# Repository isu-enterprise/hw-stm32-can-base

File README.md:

# Отладочная плата для хакинга CAN-шины

## Схема ....

### Useful docs

https://tuxotronic.org/post/mecrisp-forth/  (Loading programs via ```folie```)
https://github.com/juju2013/folie - folie

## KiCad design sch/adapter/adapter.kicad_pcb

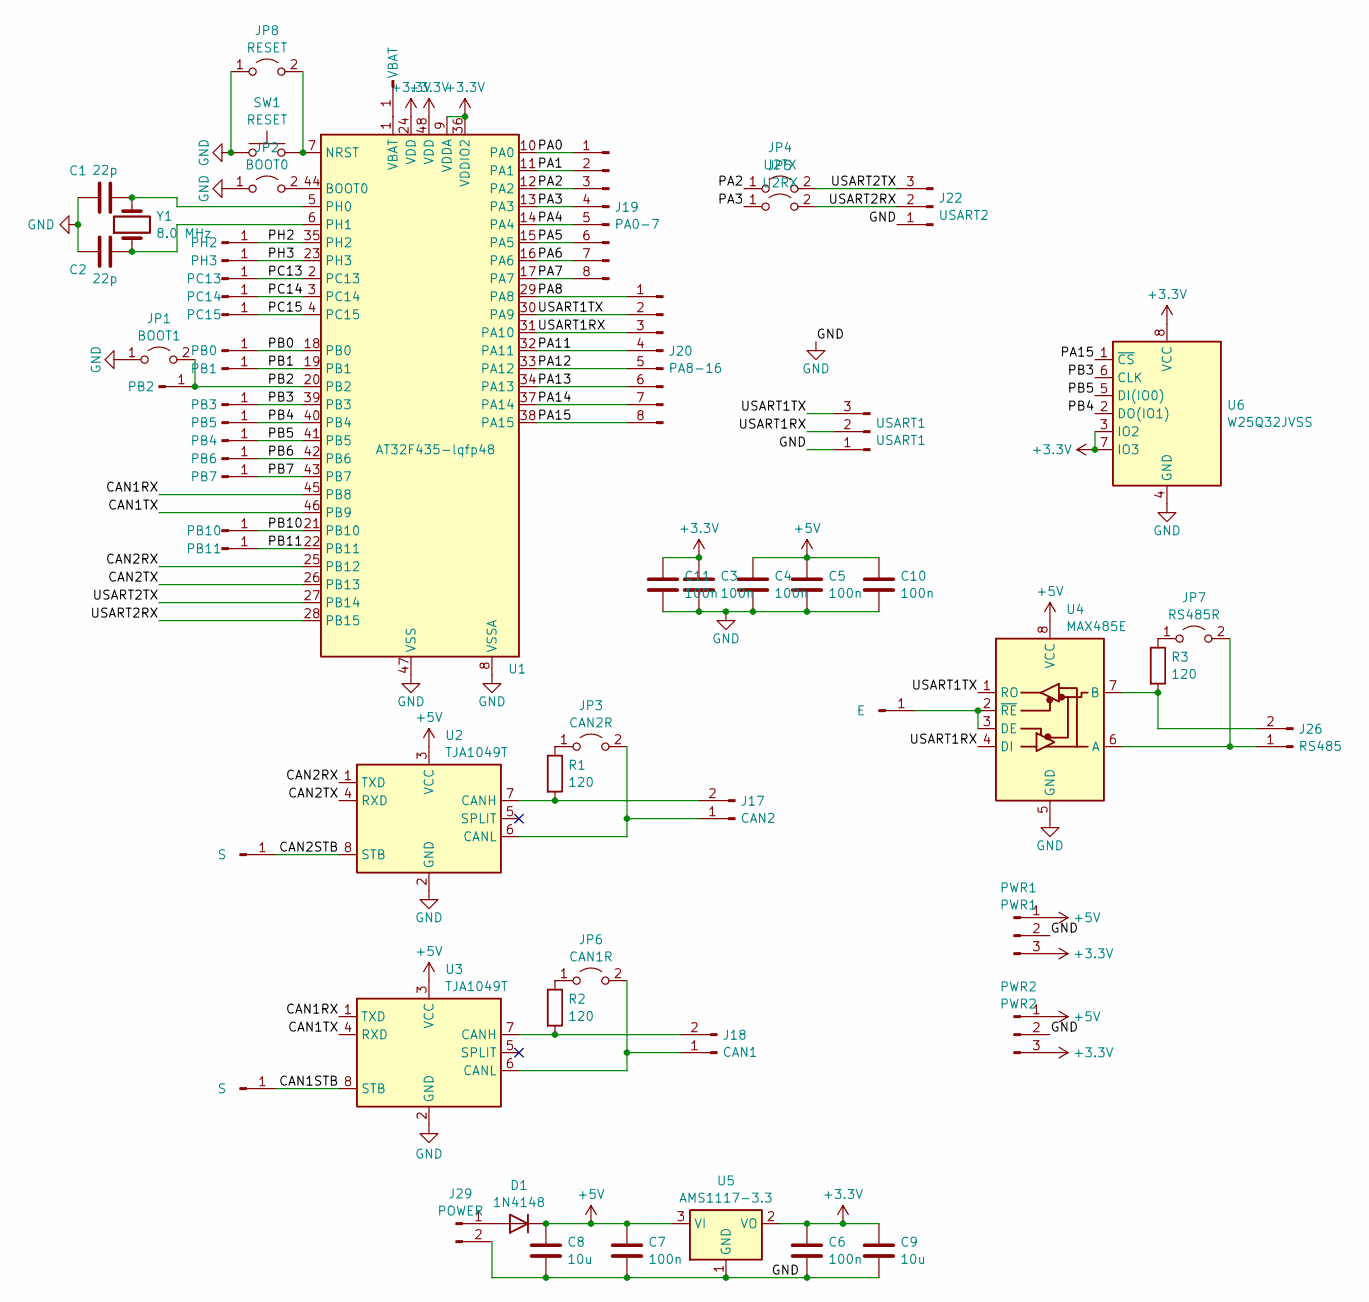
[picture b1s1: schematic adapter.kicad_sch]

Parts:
C1, C2: 22p; C_0805_2012Metric
C3, C4, C5, C6, C7, C10, C11: 100n; C_0805_2012Metric
C8, C9: 10u; C_0805_2012Metric
D1: 1N4148; D_DO-35_SOD27_P3.81mm_Vertical_KathodeUp
E: PinHeader_1x01_P2.54mm_Vertical
J17: CAN2; PinHeader_1x02_P2.54mm_Vertical
J18: CAN1; PinHeader_1x02_P2.54mm_Vertical
J19: PA0-7; PinHeader_1x08_P2.54mm_Vertical
J20: PA8-16; PinHeader_1x08_P2.54mm_Vertical
J22: USART2; PinHeader_1x03_P2.54mm_Vertical
J26: RS485; PinHeader_1x02_P2.54mm_Vertical
J29: POWER; PinHeader_1x02_P2.54mm_Vertical
JP1: BOOT1; PinHeader_1x02_P2.54mm_Vertical
JP2: BOOT0; PinHeader_1x02_P2.54mm_Vertical
JP3: CAN2R; PinHeader_1x02_P2.54mm_Vertical
JP4: U2TX; PinHeader_1x02_P2.54mm_Vertical
JP5: U2RX; PinHeader_1x02_P2.54mm_Vertical
JP6: CAN1R; PinHeader_1x02_P2.54mm_Vertical
JP7: RS485R; PinHeader_1x02_P2.54mm_Vertical
JP8: RESET; PinHeader_1x02_P2.54mm_Vertical
PB0, PB1, PB2, PB3, PB4, PB5, PB6, PB7, PB10, PB11: PinHeader_1x01_P2.54mm_Vertical
PC13, PC14, PC15: PinHeader_1x01_P2.54mm_Vertical
PH2, PH3: PinHeader_1x01_P2.54mm_Vertical
PWR1: PWR1; PinHeader_1x03_P2.54mm_Vertical
PWR2: PWR2; PinHeader_1x03_P2.54mm_Vertical
R1, R2, R3: 120; R_0805_2012Metric
S: PinHeader_1x01_P2.54mm_Vertical
SW1: RESET; SW_Push_SPST_NO_Alps_SKRK
U1: AT32F435-lqfp48; LQFP-48_7x7mm_P0.5mm
U2, U3: TJA1049T; SOIC-8_3.9x4.9mm_P1.27mm
U4: MAX485E; SOIC-8_3.9x4.9mm_P1.27mm
U5: AMS1117-3.3; SOT-223-3_TabPin2
U6: W25Q32JVSS; SOIC-8_5.23x5.23mm_P1.27mm
USART1: USART1; PinHeader_1x03_P2.54mm_Vertical
VBAT: PinHeader_1x01_P2.54mm_Vertical
Y1: 8.0 MHz; Crystal_HC49-4H_Vertical

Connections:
+3.3V: C3.1, C6.1, C9.1, C11.1, PWR1.3, PWR2.3, U1.9 (VDDA), U1.24 (VDD), U1.36 (VDDIO2), U1.48 (VDD), U5.2 (VO), U6.3 (IO2), U6.7 (IO3), U6.8 (VCC)
+5V: C4.1, C5.1, C7.1, C8.1, C10.1, D1.1 (K), PWR1.1, PWR2.1, U2.3 (VCC), U3.3 (VCC), U4.8 (VCC), U5.3 (VI)
/CAN1RX: U1.45 (PB8), U3.1 (TXD)
/CAN1TX: U1.46 (PB9), U3.4 (RXD)
/CAN2RX: U1.25 (PB12), U2.1 (TXD)
/CAN2TX: U1.26 (PB13), U2.4 (RXD)
/PA0: J19.1, U1.10 (PA0)
/PA1: J19.2, U1.11 (PA1)
/PA2: J19.3, JP4.1 (A), U1.12 (PA2)
/PA3: J19.4, JP5.1 (A), U1.13 (PA3)
/PA4: J19.5, U1.14 (PA4)
/PA5: J19.6, U1.15 (PA5)
/PA6: J19.7, U1.16 (PA6)
/PA7: J19.8, U1.17 (PA7)
/PA8: J20.1, U1.29 (PA8)
/PA11: J20.4, U1.32 (PA11)
/PA12: J20.5, U1.33 (PA12)
/PA13: J20.6, U1.34 (PA13)
/PA14: J20.7, U1.37 (PA14)
/PA15: J20.8, U1.38 (PA15), U6.1 (~CS)
/PB0: PB0.1, U1.18 (PB0)
/PB1: PB1.1, U1.19 (PB1)
/PB2: JP1.2 (B), PB2.1, U1.20 (PB2)
/PB3: PB3.1, U1.39 (PB3), U6.6 (CLK)
/PB4: PB5.1, U1.40 (PB4), U6.2 (DO(IO1))
/PB5: PB4.1, U1.41 (PB5), U6.5 (DI(IO0))
/PB6: PB6.1, U1.42 (PB6)
/PB7: PB7.1, U1.43 (PB7)
/PB10: PB10.1, U1.21 (PB10)
/PB11: PB11.1, U1.22 (PB11)
/PC13: PC13.1, U1.2 (PC13)
/PC14: PC14.1, U1.3 (PC14)
/PC15: PC15.1, U1.4 (PC15)
/PH2: PH2.1, U1.35 (PH2)
/PH3: PH3.1, U1.23 (PH3)
/USART1RX: J20.3, U1.31 (PA10), U4.4 (DI), USART1.2
/USART1TX: J20.2, U1.30 (PA9), U4.1 (RO), USART1.3
/USART2RX: J22.2, JP5.2 (B), U1.28 (PB15)
/USART2TX: J22.3, JP4.2 (B), U1.27 (PB14)
GND: C1.1, C2.1, C3.2, C4.2, C5.2, C6.2, C7.2, C8.2, C9.2, C10.2, C11.2, J22.1, J29.2, JP1.1 (A), JP2.1 (A), JP8.1 (A), PWR1.2, PWR2.2, SW1.1, U1.8 (VSSA), U1.47 (VSS), U2.2 (GND), U3.2 (GND), U4.5 (GND), U5.1 (GND), U6.4 (GND), USART1.1
unnamed: D1.2 (A), J29.1
unnamed: U1.1 (VBAT), VBAT.1
unnamed: J17.1, JP3.2 (B), U2.6 (CANL)
unnamed: J17.2, R1.2, U2.7 (CANH)
unnamed: J18.1, JP6.2 (B), U3.6 (CANL)
unnamed: J18.2, R2.2, U3.7 (CANH)
unnamed: E.1, U4.2 (~RE), U4.3 (DE)
unnamed: J26.1, JP7.2 (B), U4.6 (A)
unnamed: J26.2, R3.2, U4.7 (B)
unnamed: JP2.2 (B), U1.44 (BOOT0)
unnamed: JP3.1 (A), R1.1
unnamed: JP6.1 (A), R2.1
unnamed: JP7.1 (A), R3.1
unnamed: JP8.2 (B), SW1.2, U1.7 (NRST)
unnamed: C1.2, U1.5 (PH0), Y1.2
unnamed: C2.2, U1.6 (PH1), Y1.1

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
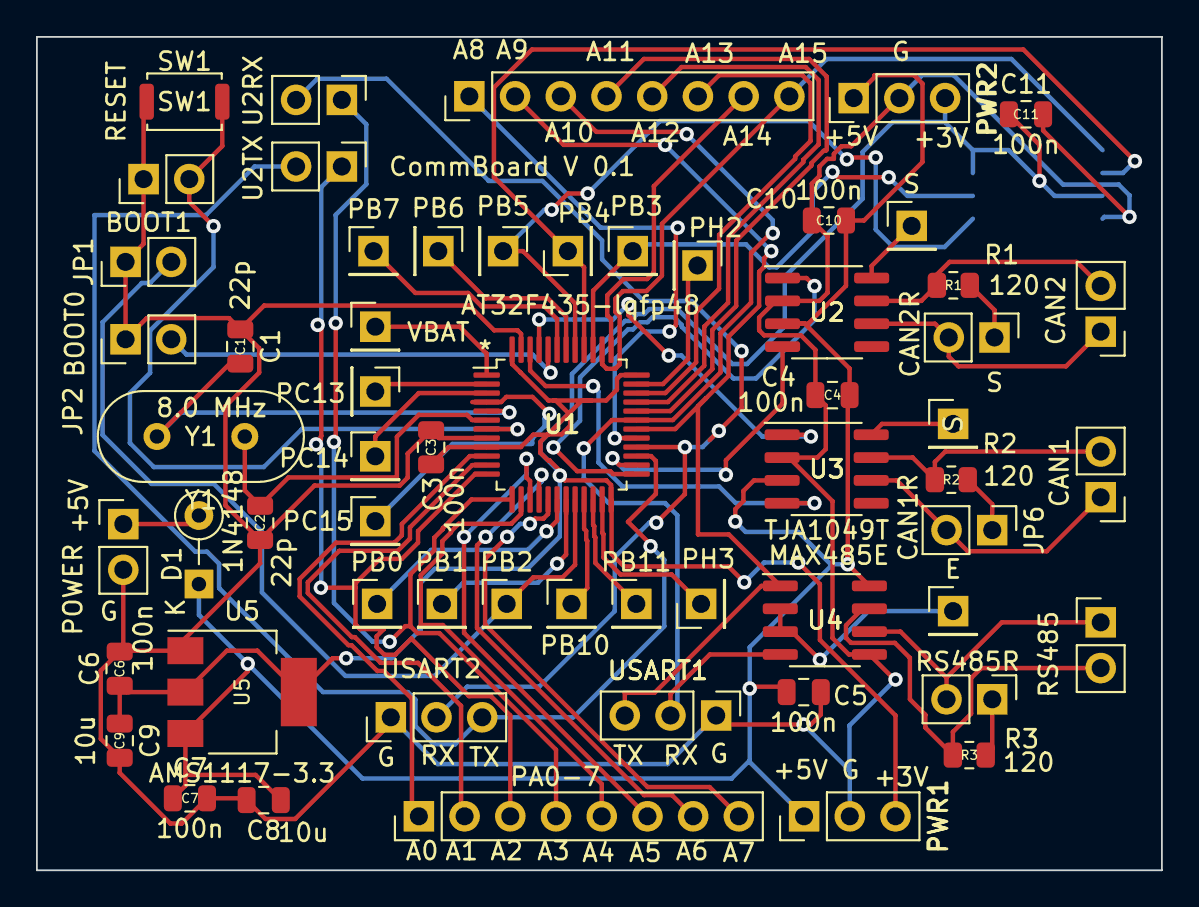
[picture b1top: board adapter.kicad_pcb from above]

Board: 2 copper layers, 62.5 x 46.3 mm, 60 parts (1 on the bottom side), 58 nets.

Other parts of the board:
S#2: PinHeader_1x01_P2.54mm_Vertical

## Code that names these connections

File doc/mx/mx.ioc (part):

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Mcu.Name=STM32F411C(C-E)Ux
Mcu.Package=UFQFPN48
Mcu.UserName=STM32F411CEUx
PA2.Mode=Asynchronous
PA2.Signal=USART2_TX
PA3.Mode=Asynchronous
PA3.Signal=USART2_RX
PA4.Signal=SPI1_NSS
PA5.Mode=Full_Duplex_Slave
PA5.Signal=SPI1_SCK
PA6.Mode=Full_Duplex_Slave
PA6.Signal=SPI1_MISO
PA7.Mode=Full_Duplex_Slave
PA7.Signal=SPI1_MOSI
PC13-ANTI_TAMP.Signal=GPIO_Output
PC14-OSC32_IN.Signal=GPIO_Output
PC15-OSC32_OUT.Signal=GPIO_Output
RCC.HSE_VALUE=25000000
RCC.SYSCLKFreq_VALUE=16000000
board=custom

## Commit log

2021-08-07 Added STM32F411 stuff to pivot to cardio.
2021-08-11 Test of led is successful.
2021-08-11 Added a figure for what....
2021-08-13 Implemented blinky
2021-08-13 Added a figure.
2021-08-13 First success of spi initialization
2021-08-14 Code generated by CubeMX
2021-08-14 Added normal/awesome book on STM32
2021-08-14 No track drivers, which were downloaded
2021-08-17 More info and SVGs of PCB.
2021-08-17 Added program for AD73360
2021-08-17 Added I2C for PCF8574t abd ILI9488
2021-08-17 Mapped Ports for TFT
2021-08-17 Added a register for RCC to support enabling I2C1
2021-08-18 Added SPI3 implementatio for 74LS595
2021-08-18 Refined setups.
2021-10-28 Correct Bug of WRONG AF code to 6
2021-10-28 Date stamp
2021-10-28 New Doc added.
2021-10-30 Added non-working MCP23s17 driver
2021-10-30 Corrected a bug in bit clearing
2021-10-30 Corrected number formats.
2021-10-31 MCP now work with big delays due to slow CS control.
2021-10-31 Now communication is working.
2021-10-31 Set a set of register names.
2021-10-31 Done with protocol implementation.
2021-10-31 Marked similar ili9488 functions with !
2021-10-31 Found an init sequence for ili9488!
2021-11-01 Initial sequence for ili9488
2021-11-01 It works, but color coding is mystical.
2021-11-07 Trying to get back to Shift register.
2021-11-08 Final stupidity finished.
2021-11-09 Working 595.
2021-11-11 Wrong clear direction
2021-11-11 Added tft implementation for 595 register. Does not work.
2021-11-11 Colors seem to work in inverse mode.
2021-11-11 Implemented alternation of registers when writing in MCP23S17.
2021-11-11 Made conserve protocol for pixel.
2021-11-12 Implemented filling rectangles.
2021-11-12 H- and V-lines now work
2021-11-13 Added compressed font.
2021-11-13 Allow font to go to flash.
2021-11-13 Font now in flash
2021-11-13 Removed wrong font
2021-11-13 Now we can print characters.
2021-11-14 Implemented typing.
2021-11-14 File Names refactoring
2021-11-17 Fixed comments for new Mecrisp Forth input buffer size
2021-11-17 Added possible location of folie sources
2021-11-17 Added CR, PLLCFG and CFG of RCC.
2021-11-17 Indexing of font.
2021-11-29 Tested spi.
2021-12-01 Swaped screen directions
2021-12-03 Started to implement h3 connection with stm32
2021-12-08 Added server directory
2021-12-08 Added template of api
2021-12-08 Added requirements -r
2021-12-08 Added api tests
2021-12-08 Provided run with Makefile
2021-12-10 Implemented tty interface as RESTF POST command
2021-12-10 Tests for FORTH endpoint
2021-12-14 Added forth code loading facility.
2021-12-14 Copies of classes
2021-12-14 Controlling server.
2021-12-14 Cleaned repetitions.
2021-12-14 Better error display
2021-12-14 Added finally buffer drawing.
2021-12-15 Added diploma ECG text.
2021-12-15 Now we can receive byte data!
2021-12-17 Addeded pictures of signals
2021-12-17 Added Pillow to requirements
2021-12-17 Added CLI fetures
2021-12-18 Now we can send and draw on the screen.
2021-12-18 Removed Todos.
2021-12-18 Now pictures are generated in correct bit order
2021-12-18 Added screen painting
2022-01-25 School network setup
2023-08-05 Cleaning the further unneeded data and sources
2023-08-05 Cleaning more unneeded data and sources
2023-08-05 Moved old code to a folder.
2023-08-05 Moved library as well.
2023-08-06 Added library files and gpio.
2023-08-06 Bug fixed and blinky test created.
2023-08-06 Added system setup stuff.
2023-08-06 Started SPI subsys.
2023-08-06 Transformed SPI driver from early implementations.
2023-08-07 Reorganize loading, libraries, bug fixed.
2023-08-07 Comments added.
2023-08-07 Bug in print word corrected.
2023-08-07 Implemented the command set for MCP-SPI-CAN device.
2023-08-07 Added docs for MCP2515 MCU-SPI-CAN interface.
2023-08-07 Bug fixed.
2023-08-07 Bug fixed. STM32F106 refuses to work. Shifting to F401.
2023-08-07 Added refman for dtm32f401cc.
2023-08-07 Adopted partially to F401 architecture.
2023-08-07 Added docs for F072 architecture.
2023-08-07 Further adaptation to F401
2023-08-07 Pin configuration
2023-08-14 MCP communications are OK now. Dump worked.
2023-08-14 Added docs for ARTERY chips at324xx LQFP48
2023-08-15 Added schematics.
2023-08-15 Ignoring gerbers, etc.
2023-08-15 Load SPI driver into flash, parametrized mcp access.
2023-08-15 Preparing SilkScreen
2023-08-15 Compile MCP stuff in flash.
2023-08-16 Added dump printing.
2023-08-16 Reg dump now does not init mcp's. SPI high speed works well.
2023-08-16 Flashing printing. Bug fix.
2023-08-16 Adapter application start, resetting mcp-2515 command added.
2023-08-17 Basic mcp-2515 can register inits
2023-08-18 Better program loader
2023-08-18 Current BOM
2023-08-18 initializing finalized ;-)
2023-08-18 Wait for mode change.
2023-08-20 Added setting CAN Bit time configuration.
2023-08-21 Message sending routines implemented, but not checked.
2023-08-21 Implementing send/receive cycle.
2023-08-22 Send/receive now work...partially.
2023-08-22 A "meaningful" message filling in
2023-08-22 Removed debugging trash.
2023-08-22 Decoding received id
2023-08-22 Receive-transmit are done.
2023-08-22 Added "stress" "test".
2023-08-24 Shift mcp-2515 code to the library.
2023-08-24 Implemented int-driven message receiving.
2023-08-24 A document bug
2023-08-24 Cleaning sources
2023-08-27 An utility to set 460800 bad rate.
2023-08-29 Added docs for STM32L073, cortex-m0, bootloaders
2023-08-29 Implemented a sniffer
2023-08-30 Added a snifing file.
2023-08-30 Output format changed to show source SPI MCP2515
2023-08-30 Implemented a polling sniffer.
2023-09-03 Added some interpretative information.
